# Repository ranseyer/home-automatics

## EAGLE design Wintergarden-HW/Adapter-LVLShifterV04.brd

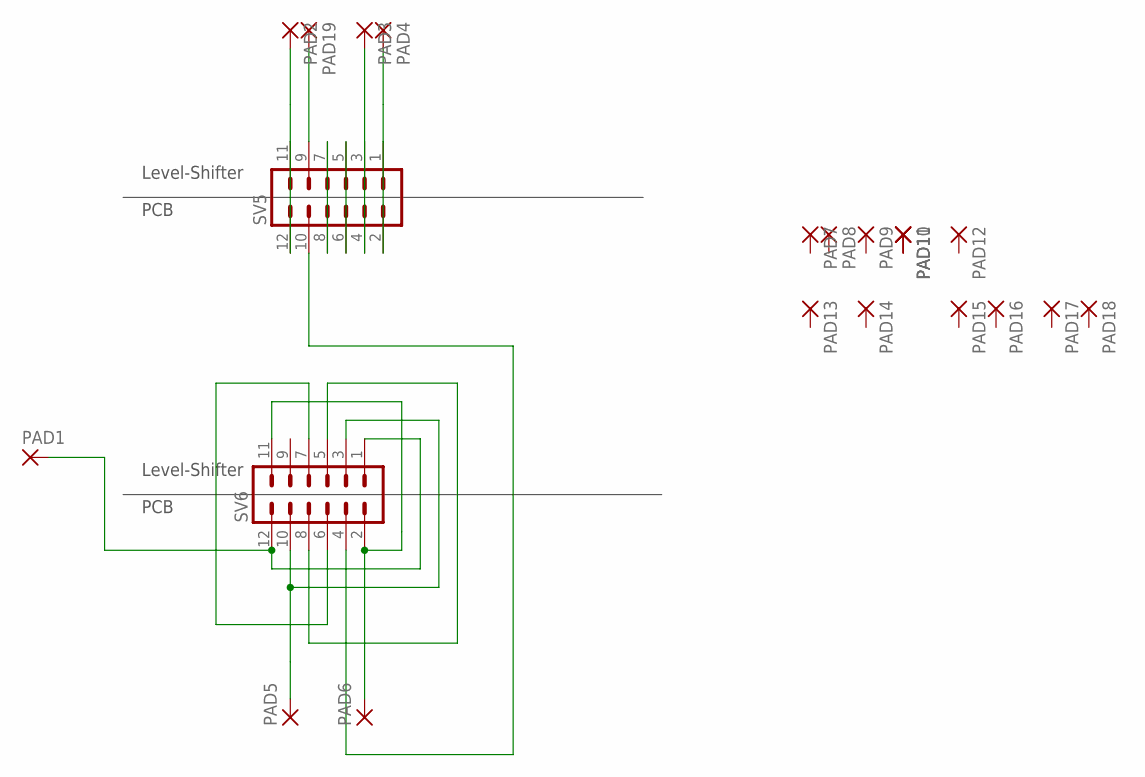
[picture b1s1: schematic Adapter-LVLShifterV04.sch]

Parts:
PAD1, PAD2, PAD3, PAD4, PAD5, PAD6, PAD7, PAD8, PAD9, PAD10, PAD11, PAD12, PAD13, PAD14, PAD15, PAD16, PAD17, PAD18, PAD19: 1,6/0,8
SV5, SV6: MA06-2

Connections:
unnamed: PAD2.1, SV5.11, SV5.12
unnamed: SV5.7, SV5.8
unnamed: SV5.5, SV5.6
unnamed: PAD4.1, SV5.1, SV5.2
unnamed: PAD6.1, SV6.2, SV6.11
unnamed: PAD1.1, SV6.1, SV6.12
unnamed: PAD5.1, SV6.3, SV6.10
unnamed: SV5.10, SV6.4
unnamed: SV6.6, SV6.7
unnamed: SV6.5, SV6.8
unnamed: PAD3.1, SV5.3, SV5.4
unnamed: PAD10.1, PAD11.1
unnamed: PAD19.1, SV5.9

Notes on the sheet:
PCB
Level-Shifter

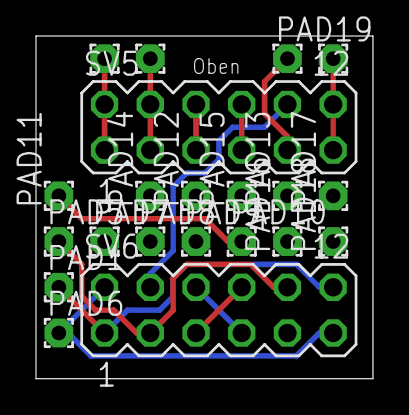
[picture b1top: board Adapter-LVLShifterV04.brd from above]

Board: 2 copper layers, 18.7 x 19.0 mm, 21 parts (0 on the bottom side), 13 nets.

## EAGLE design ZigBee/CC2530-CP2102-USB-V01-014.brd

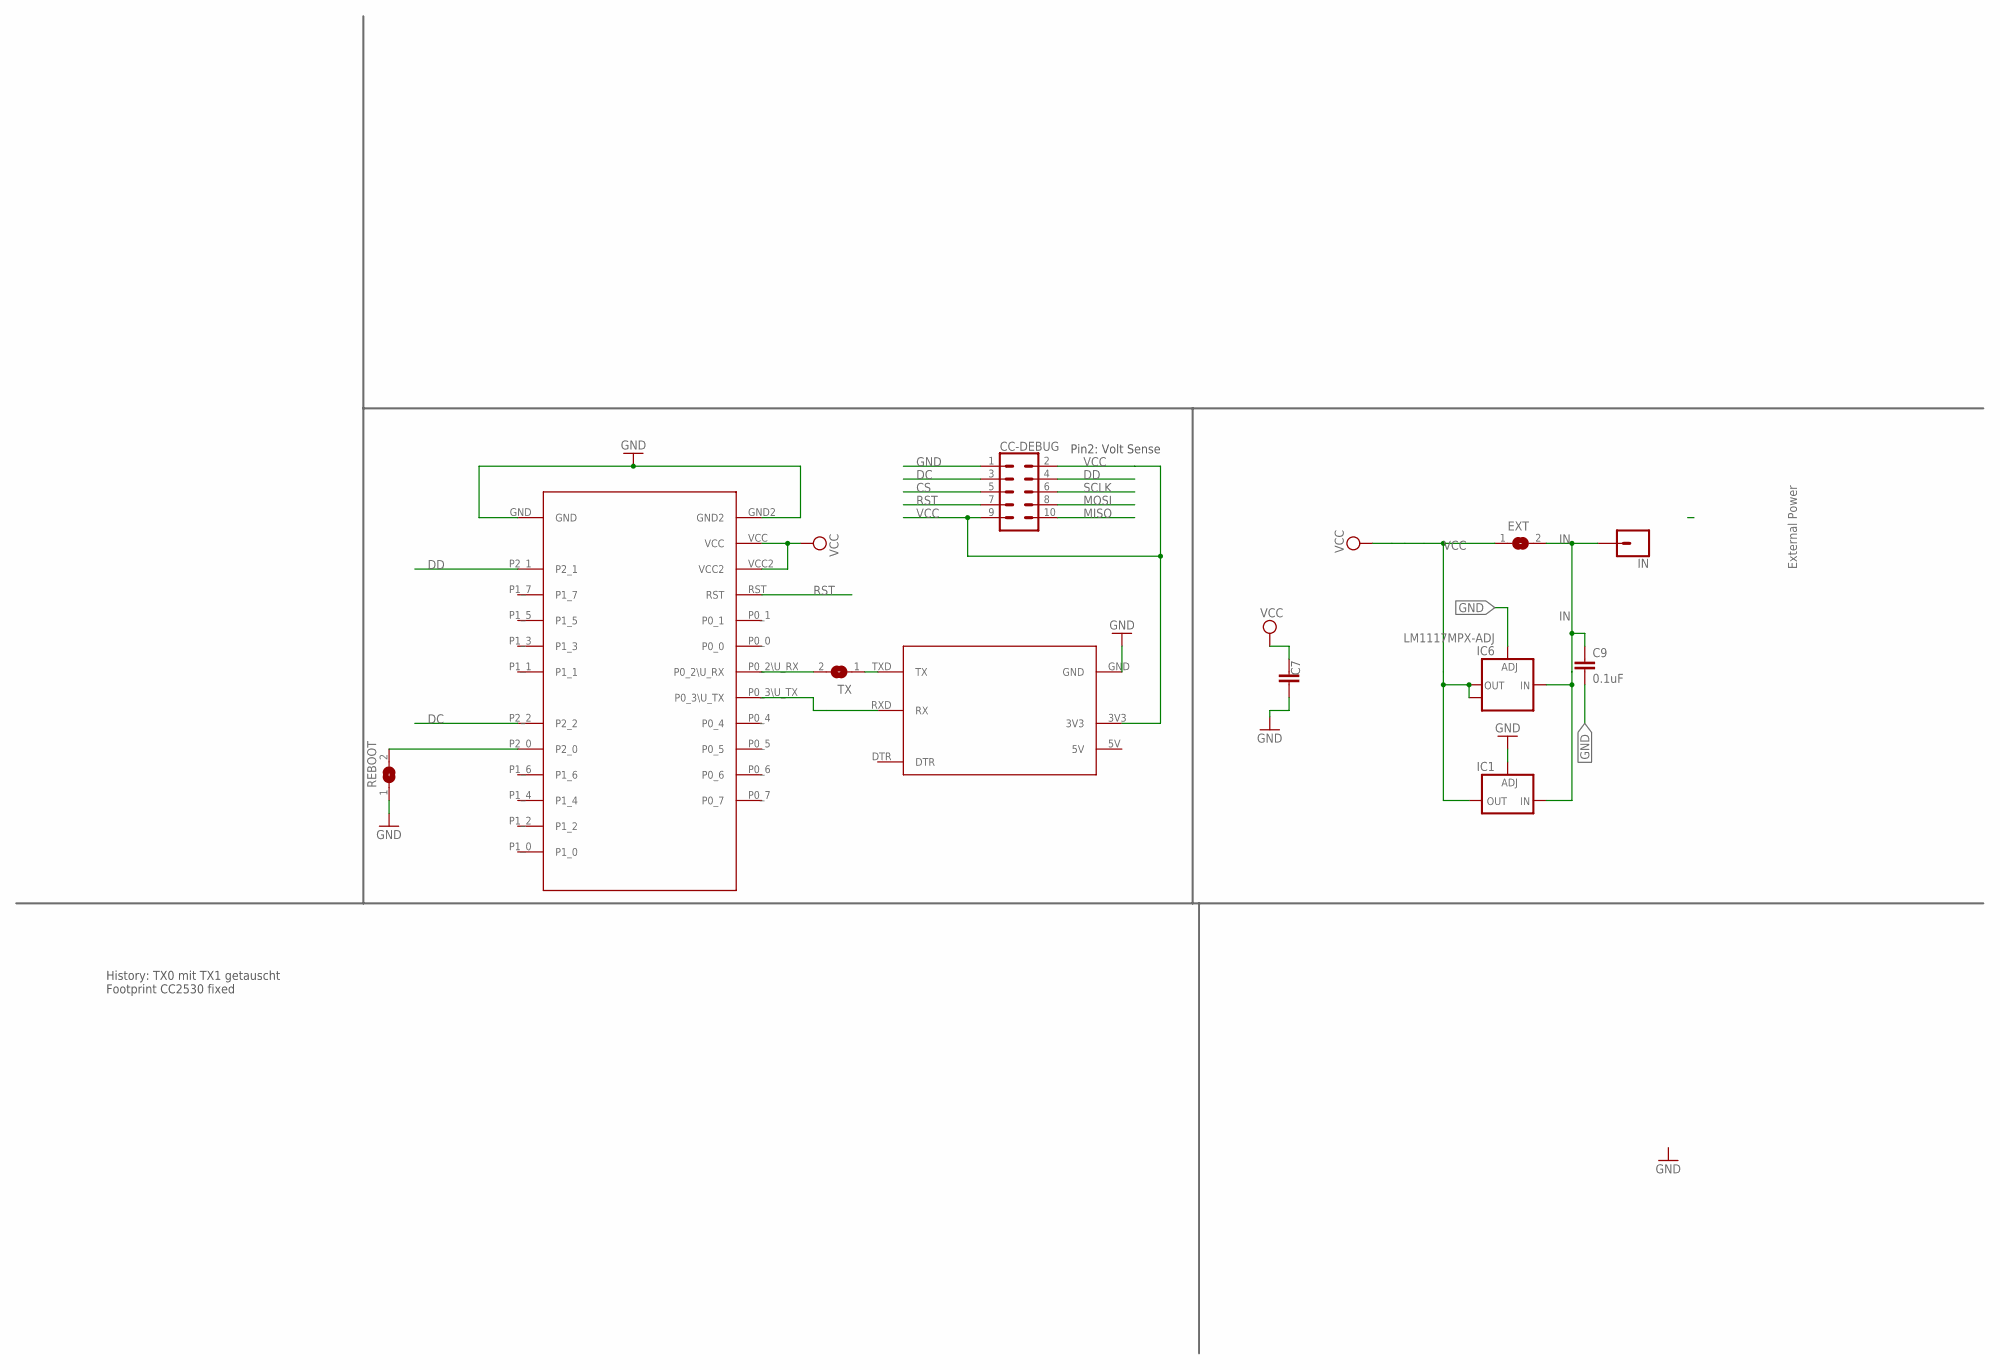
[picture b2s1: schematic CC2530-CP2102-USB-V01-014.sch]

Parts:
C7: C-EUC1812; C1812
C9: 0.1uF; C1206
CC-DEBUG: CONN_05X2SHD_LOCK; 2X5-SHROUDED_LOCK
EXT: SJ
IC1: LD117ADT50TR; DPACK
IC6: LM1117MPX-ADJ; SOT223
IN: CONN_01; 1X01
REBOOT: SJ
TX: SJ
U$1: CP2101; CP2101-BEAKOUT
U$3: CC2530_MODULE; CC2530_DIL

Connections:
5V: U$1.5V
CS: CC-DEBUG.5
DC: CC-DEBUG.3, U$3.P2_2
DD: CC-DEBUG.4, U$3.P2_1
GND: C7.1, C9.2, CC-DEBUG.1, IC1.1 (ADJ), IC6.1 (ADJ), REBOOT.1, U$1.GND, U$3.GND, U$3.GND2
IN: C9.1, EXT.2, IC1.3 (IN), IC6.3 (IN), IN.1
MISO: CC-DEBUG.10
MOSI: CC-DEBUG.8
unnamed: REBOOT.2, U$3.P2_0
unnamed: TX.2, U$3.P0_2\U_RX
unnamed: U$1.RXD (RX), U$3.P0_3\U_TX
unnamed: TX.1, U$1.TXD (TX)
RST: CC-DEBUG.7, U$3.RST
SCLK: CC-DEBUG.6
VCC: C7.2, CC-DEBUG.2, CC-DEBUG.9, EXT.1, IC1.4 (OUT), IC6.2 (OUT), IC6.TAB (OUT1), U$1.3V3, U$3.VCC, U$3.VCC2

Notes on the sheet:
External Power
History: TX0 mit TX1 getauscht Footprint CC2530 fixed
Pin2: Volt Sense

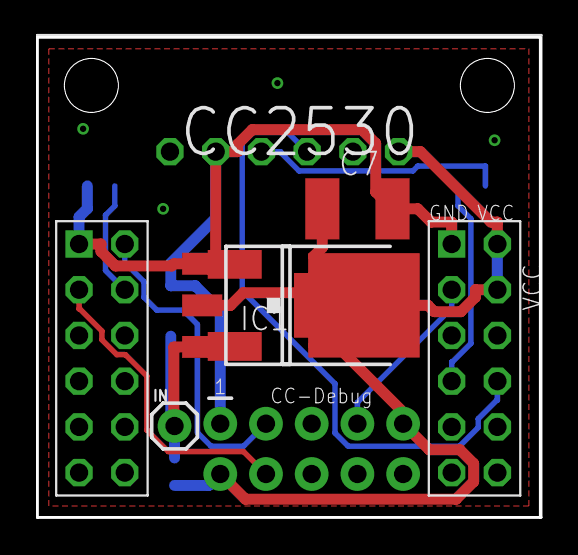
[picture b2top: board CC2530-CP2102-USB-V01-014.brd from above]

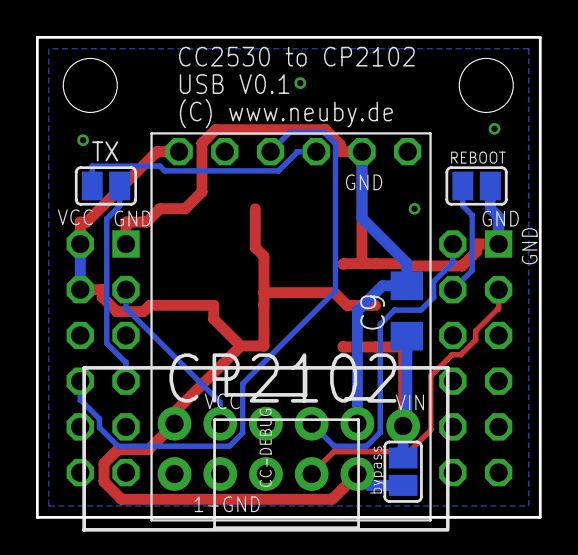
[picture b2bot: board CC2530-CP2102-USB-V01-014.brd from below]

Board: 2 copper layers, 27.9 x 26.7 mm, 11 parts (6 on the bottom side), 10 nets.

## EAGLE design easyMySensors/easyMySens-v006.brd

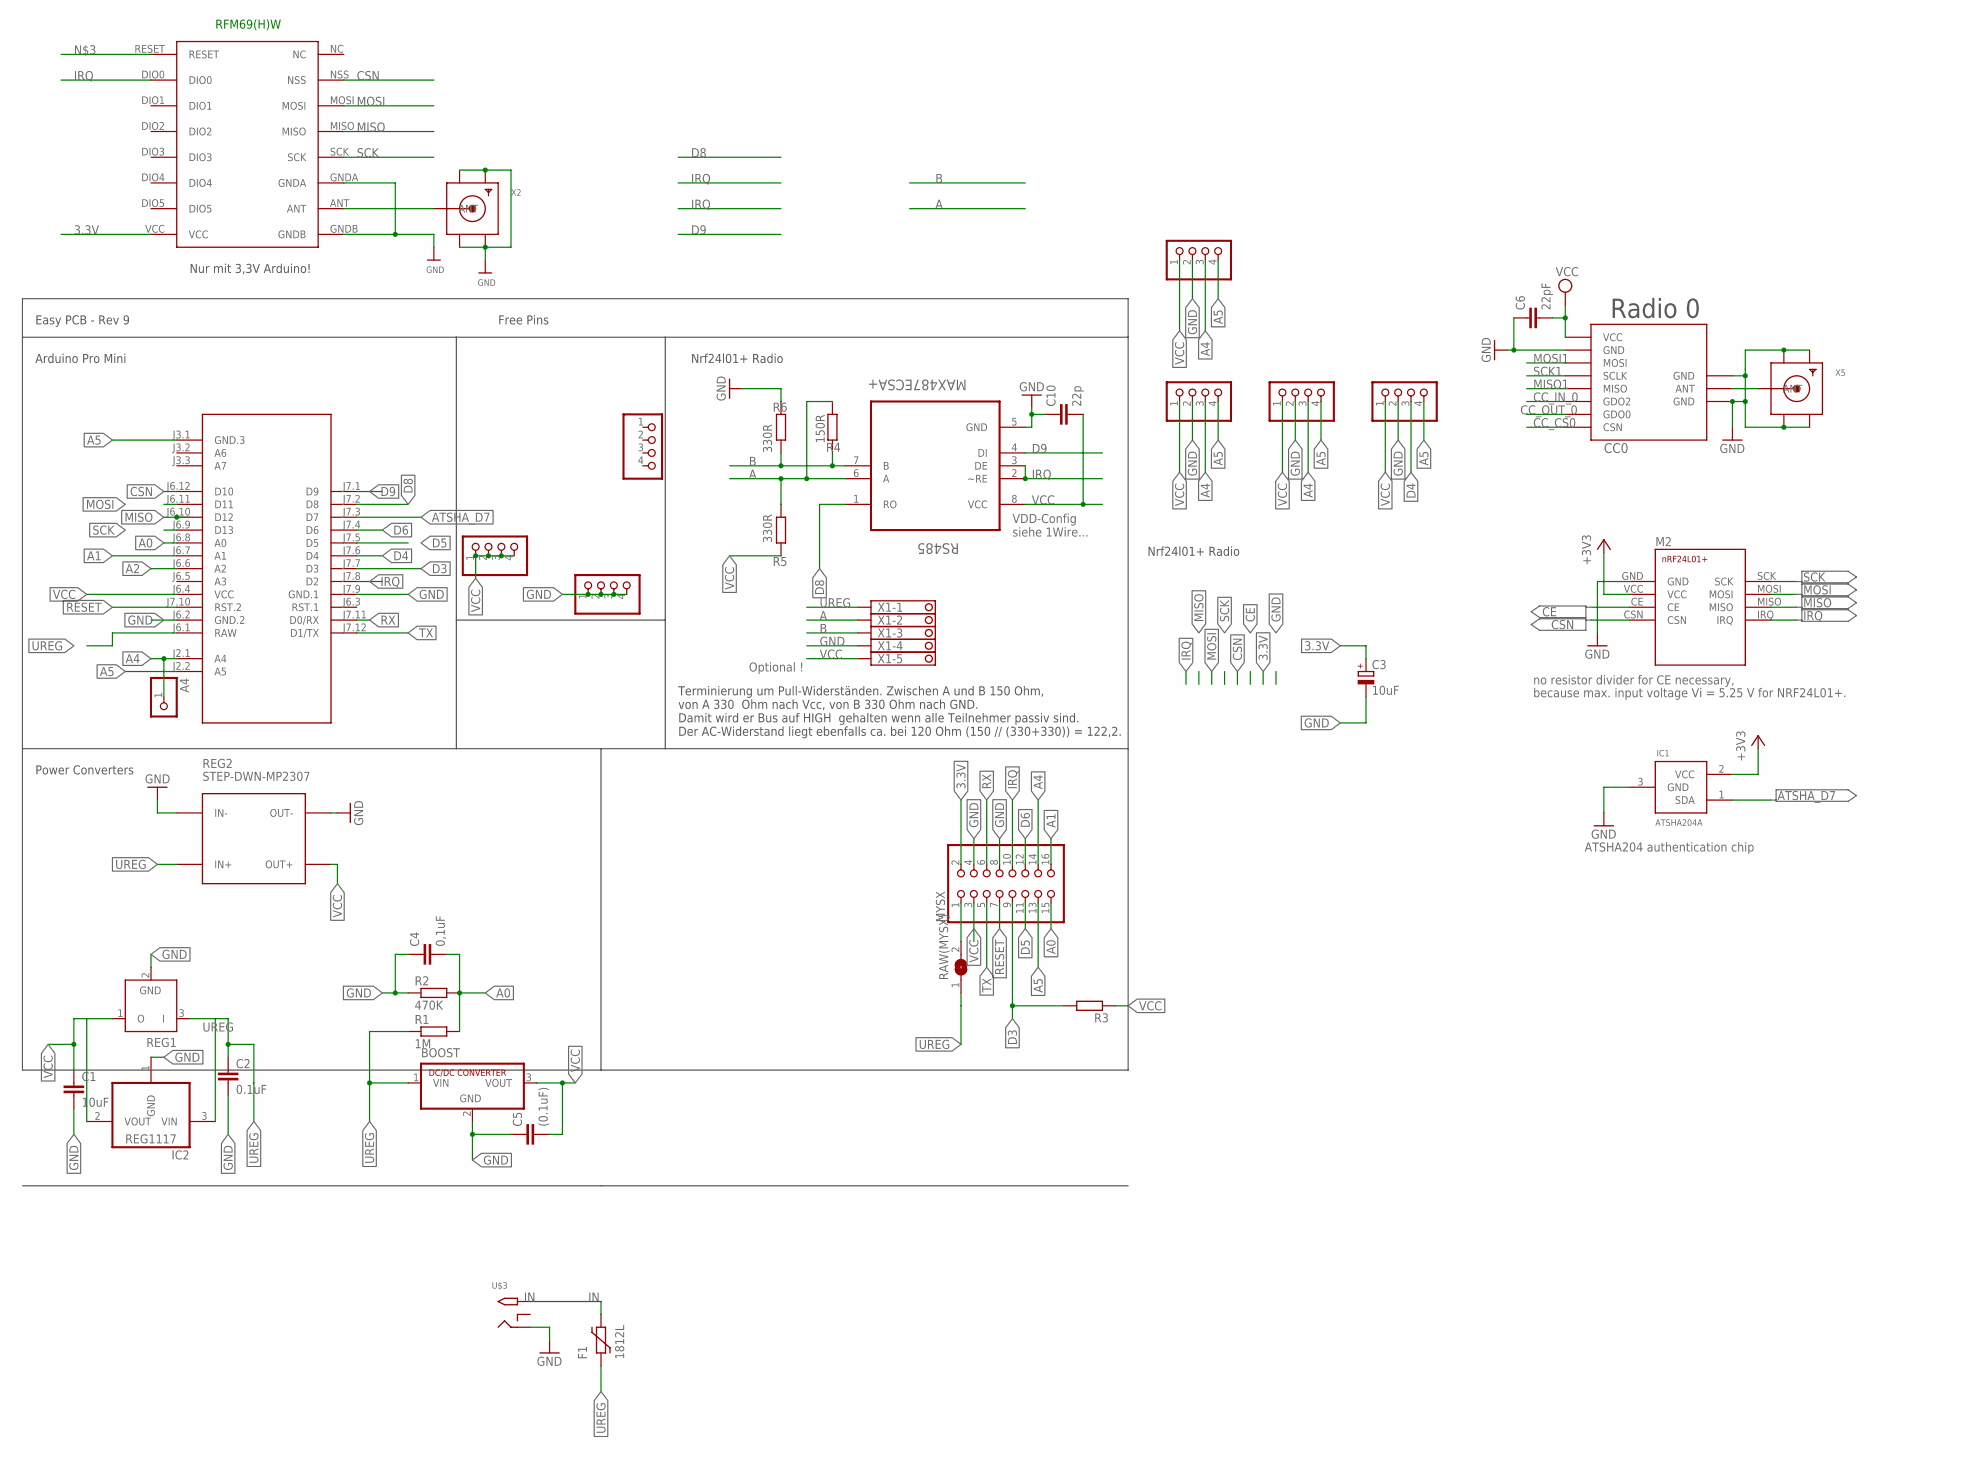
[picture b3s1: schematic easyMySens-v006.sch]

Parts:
A4: PINHD-1X1; 1X01
BH1750: PINHD-1X04_2.54-S; 1X04-S
BOOST: R-78C1.8-1.0; SIP3
C1: 10uF; C1210
C2: 0.1uF; C1206
C3: 10uF; SMC_C
C4: 0,1uF; C1206
C5: (0.1uF); C1206
C6: 22pF; C0805
C10: 22p; C0805
CC0: CC1101; CC1101_MODULE1_SMD
F1: 1812L
I2C-1, I2C-2: PINHD-1X04_2.54-S; 1X04-S
IC1: ATSHA204A; SOT23
IC2: REG1117; SOT223
JP1, JP3, JP12: PINHD-1X04_2.54-S; 1X04-S
M1: ARDUINO-PRO-MINI-3.3V#NP; ARDUINO-PRO-MINI#NP
M2: NRF24L01+SMD
MOTION: PINHD-1X04_2.54-S; 1X04-S
MYSX: PINHD-2X08_2.54; 2X08
R1: 1M; R0805
R2: 470K; R0805
R3: R-EU_R0805; R0805
R4: 150R; R0805
R5, R6: 330R; R0805
RAW(MYSX): SJ
REG1: LP2950Z; TO92
REG2: STEP-DWN-MP2307; DC-DC-STEP-DOWN-MP2307
RFM69W: RFM69HW; RFM
RS485: MAX487ECSA+; SOIC127P600X175-8N
U$3: 2.1MMJACKTHM; PJ-102A
X1: 1751277
X2, X5: SMACONNECTOR_EDGE; SMA_EDGELAUNCH

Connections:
3.3V: C3.+, IC1.2 (VCC), M2.VCC, MYSX.2, RFM69W.VCC
A: R4.1, R5.2, RS485.6 (A), X1.2
A0: C4.2, M1.J6.8 (A0), MYSX.15, R1.2, R2.2
A1: M1.J6.7 (A1), MYSX.16
A2: M1.J6.6 (A2)
A4: A4.1, BH1750.3, I2C-1.3, I2C-2.3, M1.J2.1 (A4), MYSX.14
A5: BH1750.4, I2C-1.4, I2C-2.4, M1.J2.2 (A5), M1.J3.1 (GND.3), MOTION.4, MYSX.13
ANT0: CC0.ANT, X5.P (ANT)
ATSHA_D7: IC1.1 (SDA), M1.J7.3 (D7)
B: R4.2, R6.1, RS485.7 (B), X1.3
CC_CS0: CC0.CSN
CC_IN_0: CC0.GDO2
CC_OUT_0: CC0.GDO0
CE: M2.CE
CSN: M1.J6.12 (D10), M2.CSN, RFM69W.NSS
D3: M1.J7.7 (D3), MYSX.9, R3.2
D4: M1.J7.6 (D4), MOTION.3
D5: M1.J7.5 (D5), MYSX.11
D6: M1.J7.4 (D6), MYSX.12
D8: M1.J7.2 (D8), RS485.1 (RO)
D9: M1.J7.1 (D9), RS485.4 (DI)
GND: BH1750.2, BOOST.2 (GND), C1.2, C2.2, C3.-, C4.1, C5.1, C6.1, C10.1, CC0.GND@0 (GND), CC0.GND@1 (GND), CC0.GND@2 (GND), I2C-1.2, I2C-2.2, IC1.3 (GND), IC2.1 (GND), JP1.1, JP1.2, JP1.3, JP1.4, M1.J6.2 (GND.2), M1.J7.9 (GND.1), M2.GND, MOTION.2, MYSX.4, MYSX.8, R2.1, R6.2, REG1.2 (GND), REG2.IN-, REG2.OUT-, RFM69W.GNDA, RFM69W.GNDB, RS485.5 (GND), U$3.RING, X1.4, X2.GND@1 (GND4), X2.GND@2 (GND3), X2.GND@3 (GND2), X2.GND@4 (GND1), X5.GND@1 (GND4), X5.GND@2 (GND3), X5.GND@3 (GND2), X5.GND@4 (GND1)
IN: F1.P$2 (2), U$3.TIP
IRQ: M1.J7.8 (D2), M2.IRQ, MYSX.10, RFM69W.DIO0, RS485.2 (~RE), RS485.3 (DE)
MISO: M1.J6.10 (D12), M2.MISO, RFM69W.MISO
MISO1: CC0.MISO
MOSI: M1.J6.11 (D11), M2.MOSI, RFM69W.MOSI
MOSI1: CC0.MOSI
unnamed: MYSX.1, RAW(MYSX).2
unnamed: RFM69W.ANT, X2.P (ANT)
RESET: M1.J7.10 (RST.2), MYSX.7
RX: M1.J7.11 (D0/RX), MYSX.6
SCK: M1.J6.9 (D13), M2.SCK, RFM69W.SCK
SCK1: CC0.SCLK
TX: M1.J7.12 (D1/TX), MYSX.5
UREG: BOOST.1 (VIN), C2.1, F1.P$1 (1), IC2.3 (VIN), M1.J6.1 (RAW), R1.1, RAW(MYSX).1, REG1.3 (I), REG2.IN+, X1.1
VCC: BH1750.1, BOOST.3 (VOUT), C1.1, C5.2, C6.2, C10.2, CC0.VCC, I2C-1.1, I2C-2.1, IC2.2 (VOUT), JP3.1, JP3.2, JP3.3, JP3.4, M1.J6.4 (VCC), MOTION.1, MYSX.3, R3.1, R5.1, REG1.1 (O), REG2.OUT+, RS485.8 (VCC), X1.5

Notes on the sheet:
Easy PCB - Rev 9
Arduino Pro Mini
Free Pins
Nrf24l01+ Radio
Power Converters
VDD-Config siehe 1Wire...
Optional !
no resistor divider for CE necessary,
because max. input voltage Vi = 5.25 V for NRF24L01+.
ATSHA204 authentication chip
RFM69(H)W
Nur mit 3,3V Arduino!
Radio 0
Terminierung um Pull-Widerständen. Zwischen A und B 150 Ohm, von A 330 Ohm nach Vcc, von B 330 Ohm nach GND. Damit wird er Bus auf HIGH gehalten wenn alle Teilnehmer passiv sind. Der AC-Widerstand liegt ebenfalls ca. bei 120 Ohm (150 // (330+330)) = 122,2.

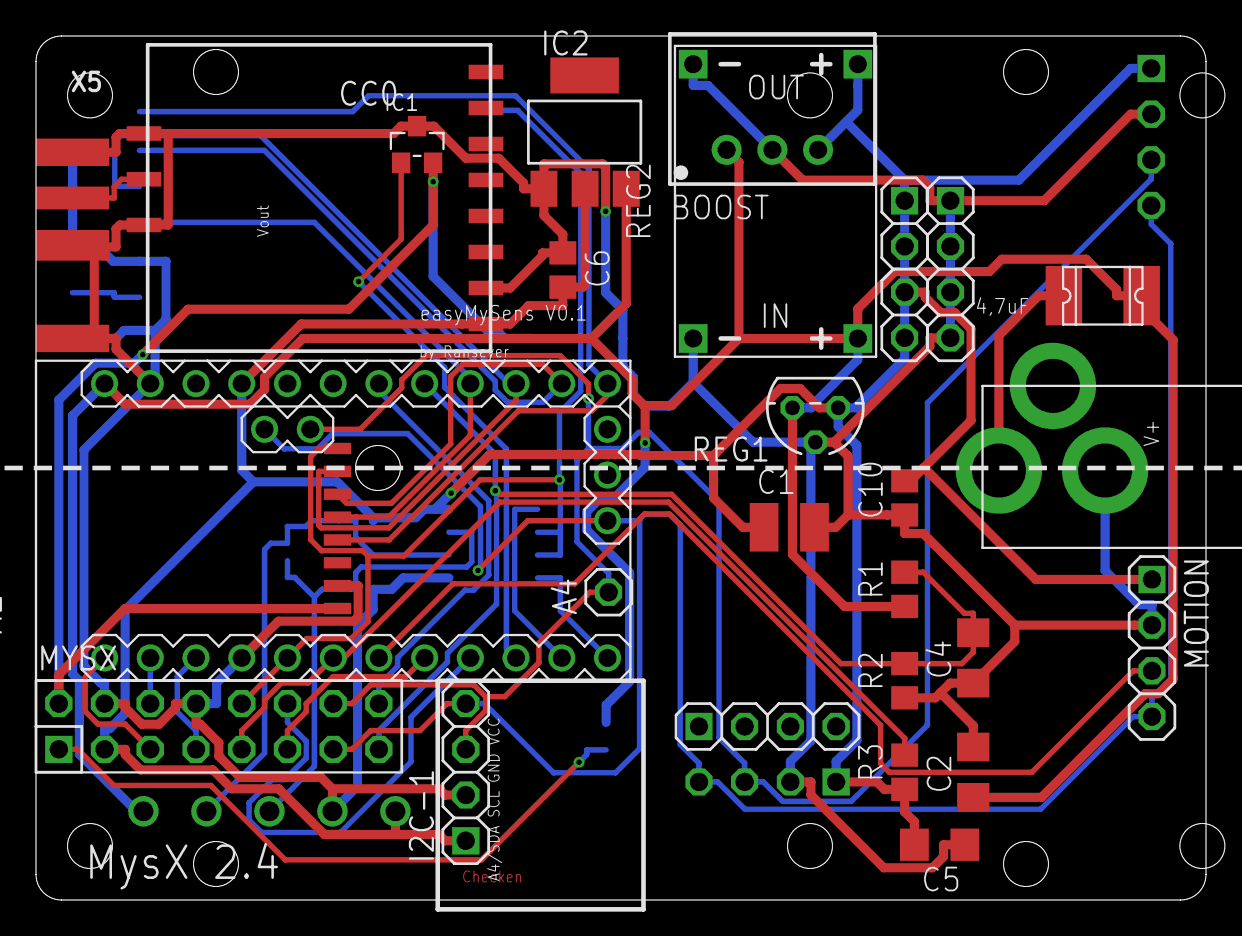
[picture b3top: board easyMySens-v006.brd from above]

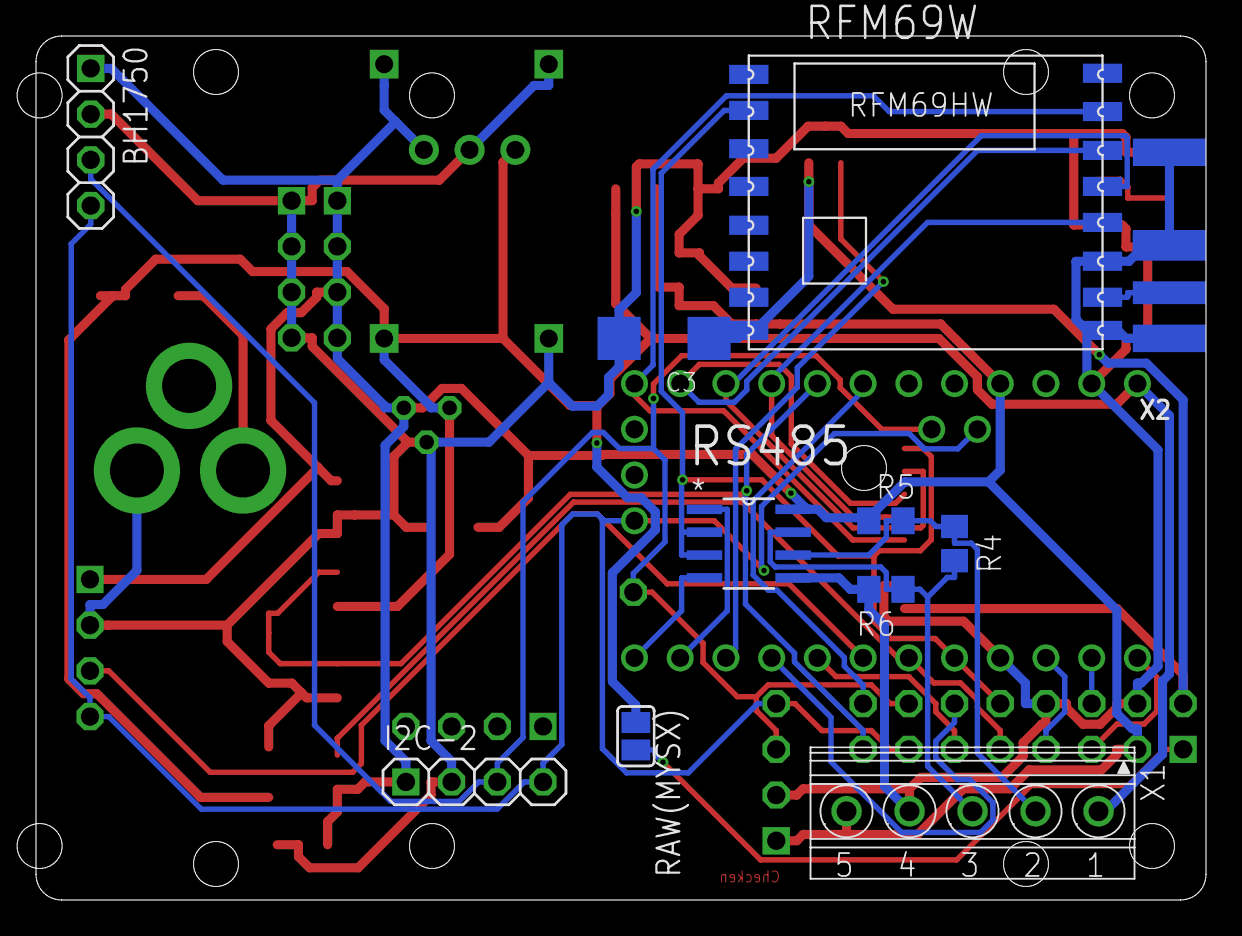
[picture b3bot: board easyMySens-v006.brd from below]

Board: 2 copper layers, 65.0 x 48.0 mm, 38 parts (11 on the bottom side), 29 nets.

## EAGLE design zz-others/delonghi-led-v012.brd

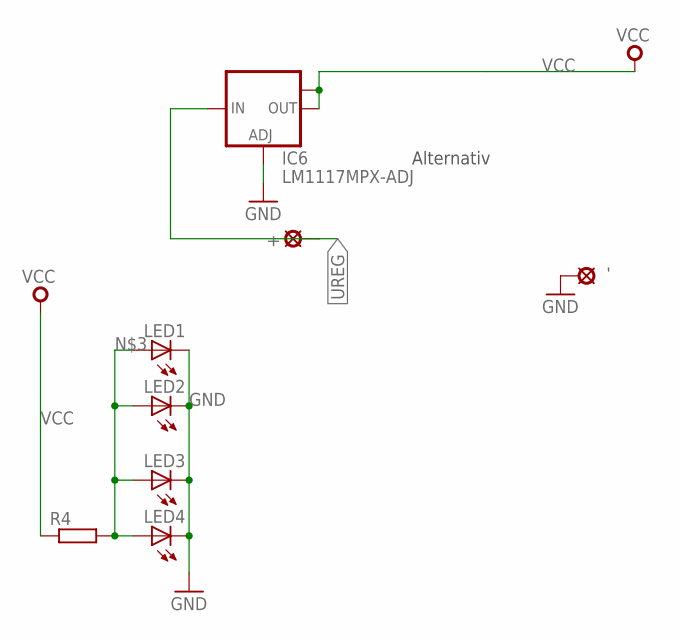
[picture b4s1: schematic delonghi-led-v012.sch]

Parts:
+: LSP10
-: LSP10
IC6: LM1117MPX-ADJ; SOT223
LED1, LED2, LED3, LED4: LEDCHIPLED_0805; CHIPLED_0805
R4: R-EU_M0805; M0805

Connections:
GND: -.MP, IC6.1 (ADJ), LED1.C, LED2.C, LED3.C, LED4.C
unnamed: LED1.A, LED2.A, LED3.A, LED4.A, R4.2
UREG: +.MP, IC6.3 (IN)
VCC: IC6.2 (OUT), IC6.TAB (OUT1), R4.1

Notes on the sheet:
Alternativ

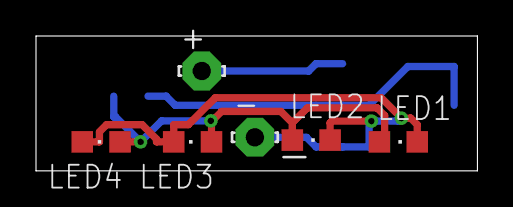
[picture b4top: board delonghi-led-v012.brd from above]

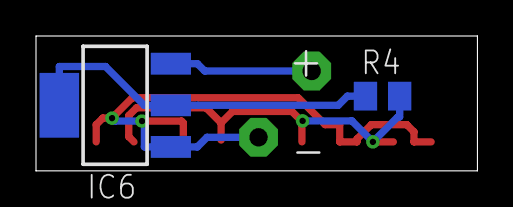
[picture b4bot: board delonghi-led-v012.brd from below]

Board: 2 copper layers, 24.5 x 7.5 mm, 8 parts (2 on the bottom side), 4 nets.

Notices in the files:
parts and their libraries:
SparkFun-Connectors: Licensing: Creative Commons ShareAlike 4.0 International - https://creativecommons.org/licenses/by-sa/4.0
diy-modules: Released under the Creative Commons Attribution 4.0 International License: http://creativecommons.org/licenses/by/4.0
